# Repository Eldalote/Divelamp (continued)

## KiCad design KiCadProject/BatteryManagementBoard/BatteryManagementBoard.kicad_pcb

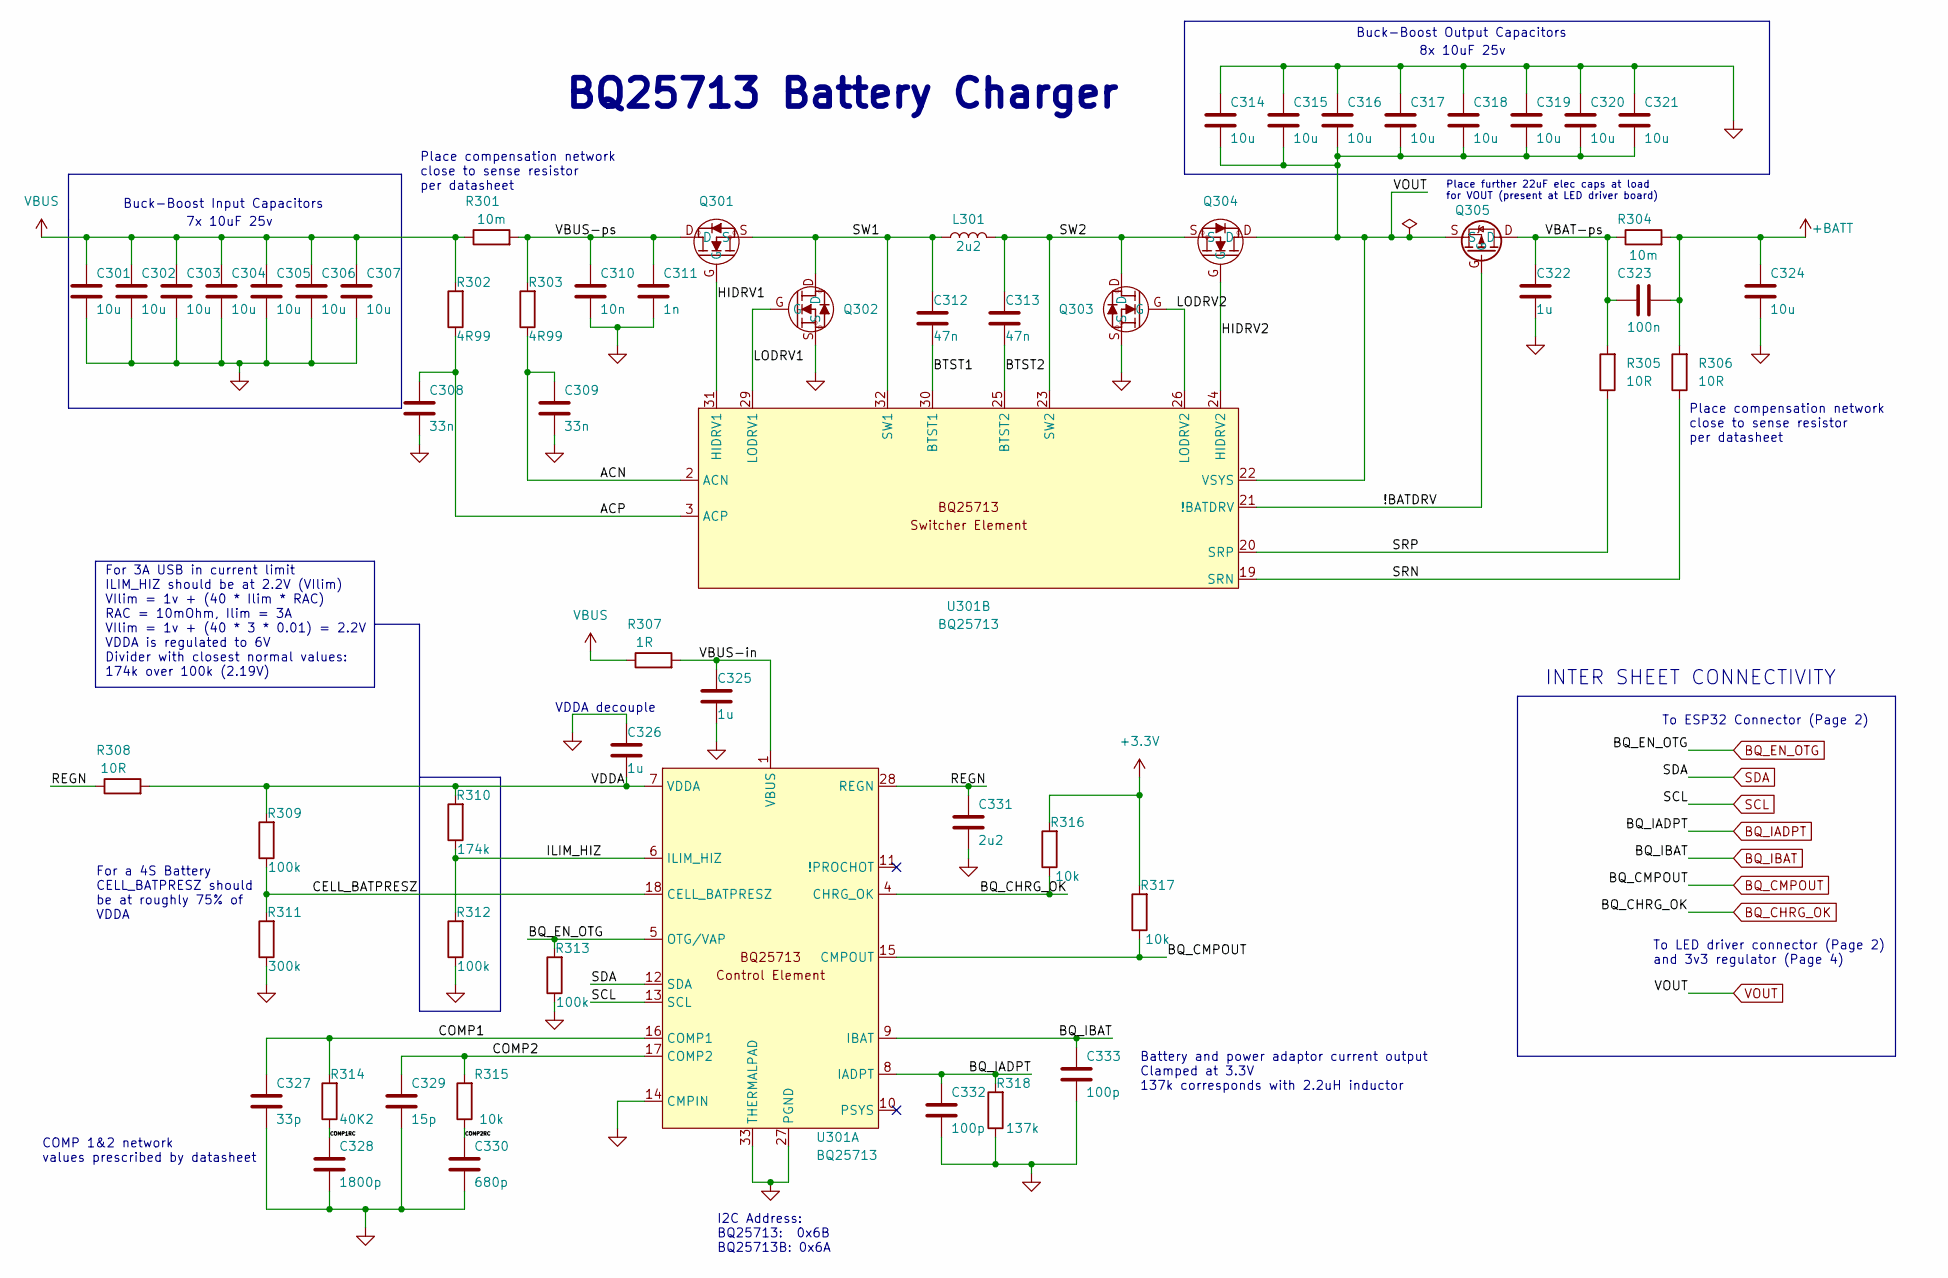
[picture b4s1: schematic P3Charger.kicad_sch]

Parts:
C301, C302, C303, C304, C305, C306, C307, C314, C315, C316, C317, C318, C319, C320, C321, C324: 10u; C_0805_2012Metric
C308, C309: 33n; C_0402_1005Metric
C310: 10n; C_0402_1005Metric
C311: 1n; C_0402_1005Metric
C312, C313: 47n; C_0402_1005Metric
C322, C325, C326: 1u; C_0603_1608Metric
C323: 100n; C_0402_1005Metric
C327: 33p; C_0402_1005Metric
C328: 1800p; C_0402_1005Metric
C329: 15p; C_0402_1005Metric
C330: 680p; C_0402_1005Metric
C331: 2u2; C_0603_1608Metric
C332, C333: 100p; C_0402_1005Metric
L301: 2u2; SRP-1265C
Q301, Q302, Q303, Q304: NFET_Gatenames; DFN3x3A_8L_EP1_P
Q305: PMOS_Gatenames; DFN3x3A_8L_EP1_P
R301, R304: 10m; R_1206_3216Metric
R302, R303: 4R99; R_0402_1005Metric
R305, R306, R308: 10R; R_0402_1005Metric
R307: 1R; R_0603_1608Metric
R309, R312, R313: 100k; R_0402_1005Metric
R310: 174k; R_0402_1005Metric
R311: 300k; R_0402_1005Metric
R314: 40K2; R_0402_1005Metric
R315, R316, R317: 10k; R_0402_1005Metric
R318: 137k; R_0402_1005Metric
U301: BQ25713; Texas_S-PWQFN-N32_EP2.8x2.8mm

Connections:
+3.3V: R316.2, R317.2; also elsewhere on the board
+BATT: C323.2, C324.1, R304.2, R306.2; also elsewhere on the board
/P3-Charger/!BATDRV: Q305.G, U301.21 (!BATDRV)
/P3-Charger/ACN: C309.1, R303.1, U301.2 (ACN)
/P3-Charger/ACP: C308.1, R302.1, U301.3 (ACP)
/P3-Charger/BTST1: C312.2, U301.30 (BTST1)
/P3-Charger/BTST2: C313.2, U301.25 (BTST2)
/P3-Charger/CELL_BATPRESZ: R309.1, R311.2, U301.18 (CELL_BATPRESZ)
/P3-Charger/COMP1: C327.1, R314.2, U301.16 (COMP1)
/P3-Charger/COMP1RC: C328.1, R314.1
/P3-Charger/COMP2: C329.1, R315.2, U301.17 (COMP2)
/P3-Charger/COMP2RC: C330.1, R315.1
/P3-Charger/HIDRV1: Q301.G, U301.31 (HIDRV1)
/P3-Charger/HIDRV2: Q304.G, U301.24 (HIDRV2)
/P3-Charger/ILIM_HIZ: R310.1, R312.2, U301.6 (ILIM_HIZ)
/P3-Charger/LODRV1: Q302.G, U301.29 (LODRV1)
/P3-Charger/LODRV2: Q303.G, U301.26 (LODRV2)
/P3-Charger/REGN: C331.1, R308.1, U301.28 (REGN)
/P3-Charger/SRN: R306.1, U301.19 (SRN)
/P3-Charger/SRP: R305.1, U301.20 (SRP)
/P3-Charger/SW1: C312.1, L301.1, Q301.S, Q302.D, U301.32 (SW1)
/P3-Charger/SW2: C313.1, L301.2, Q303.D, Q304.S, U301.23 (SW2)
/P3-Charger/VBAT-ps: C322.1, C323.1, Q305.D, R304.1, R305.2
/P3-Charger/VBUS-in: C325.1, R307.2, U301.1 (VBUS)
/P3-Charger/VBUS-ps: C310.1, C311.1, Q301.D, R301.2, R303.2
/P3-Charger/VDDA: C326.1, R308.2, R309.2, R310.2, U301.7 (VDDA)
BQ_CHRG_OK: R316.1, U301.4 (CHRG_OK); also elsewhere on the board
BQ_CMPOUT: R317.1, U301.15 (CMPOUT); also elsewhere on the board
BQ_EN_OTG: R313.2, U301.5 (OTG/VAP); also elsewhere on the board
BQ_IADPT: C332.1, R318.2, U301.8 (IADPT); also elsewhere on the board
BQ_IBAT: C333.1, U301.9 (IBAT); also elsewhere on the board
GND: C301.2, C302.2, C303.2, C304.2, C305.2, C306.2, C307.2, C308.2, C309.2, C310.2, C311.2, C314.1, C315.1, C316.1, C317.1, C318.1, C319.1, C320.1, C321.1, C322.2, C324.2, C325.2, C326.2, C327.2, C328.2, C329.2, C330.2, C331.2, C332.2, C333.2, Q302.S, Q303.S, R311.1, R312.1, R313.1, R318.1, U301.14 (CMPIN), U301.27 (PGND), U301.33 (THERMALPAD); also elsewhere on the board
SCL: U301.13 (SCL); also elsewhere on the board
SDA: U301.12 (SDA); also elsewhere on the board
VBUS: C301.1, C302.1, C303.1, C304.1, C305.1, C306.1, C307.1, R301.1, R302.2, R307.1; also elsewhere on the board
VOUT: C314.2, C315.2, C316.2, C317.2, C318.2, C319.2, C320.2, C321.2, Q304.D, Q305.S, U301.22 (VSYS); also elsewhere on the board

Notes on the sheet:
To LED driver connector (Page 2) and 3v3 regulator (Page 4)
Buck-Boost Input Capacitors
INTER SHEET CONNECTIVITY
For a 4S Battery CELL_BATPRESZ should be at roughly 75% of VDDA
7x 10uF 25v
8x 10uF 25v
COMP 1&2 network values prescribed by datasheet
Place further 22uF elec caps at load for VOUT (present at LED driver board)
BQ25713 Battery Charger
VDDA decouple
To ESP32 Connector (Page 2)
Place compensation network close to sense resistor per datasheet
Buck-Boost Output Capacitors
Battery and power adaptor current output Clamped at 3.3V 137k corresponds with 2.2uH inductor
I2C Address: BQ25713: 0x6B BQ25713B: 0x6A
For 3A USB in current limit ILIM_HIZ should be at 2.2V (VIlim) VIlim = 1v + (40 * Ilim * RAC) RAC = 10mOhm, Ilim = 3A VIlim = 1v + (40 * 3 * 0.01) = 2.2V VDDA is regulated to 6V Divider with closest normal values: 174k over 100k (2.19V)

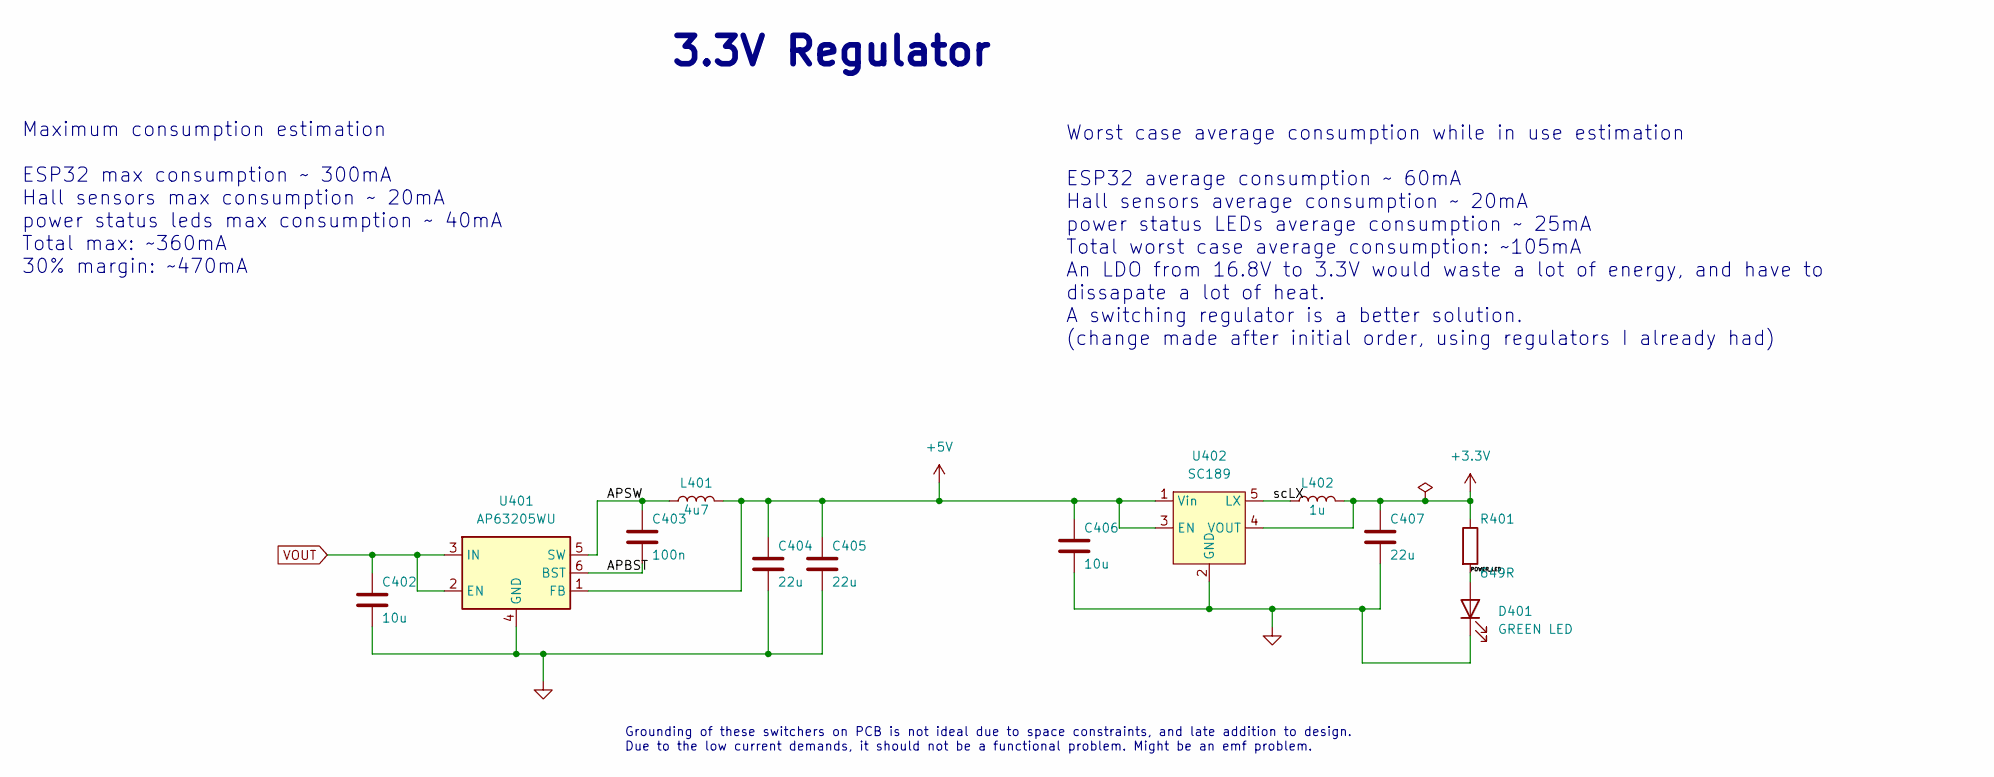
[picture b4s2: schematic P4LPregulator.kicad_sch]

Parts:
C402, C406: 10u; C_0805_2012Metric
C403: 100n; C_0402_1005Metric
C404, C405, C407: 22u; C_0805_2012Metric
D401: GREEN LED; LED_0805_2012Metric
L401: 4u7; L_1210_3225Metric
L402: 1u; L_1210_3225Metric
R401: 649R; R_0402_1005Metric
U401: AP63205WU; TSOT-23-6
U402: SC189; SOT-23-5

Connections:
+3.3V: C407.1, L402.2, R401.1, U402.4 (VOUT); also elsewhere on the board
+5V: C404.1, C405.1, C406.1, L401.2, U401.1 (FB), U402.1 (Vin), U402.3 (EN)
/P4 - 3V3 Regulator/APBST: C403.2, U401.6 (BST)
/P4 - 3V3 Regulator/APSW: C403.1, L401.1, U401.5 (SW)
/P4 - 3V3 Regulator/POWER_LED: D401.2 (A), R401.2
/P4 - 3V3 Regulator/scLX: L402.1, U402.5 (LX)
GND: C402.2, C404.2, C405.2, C406.2, C407.2, D401.1 (K), U401.4 (GND), U402.2 (GND); also elsewhere on the board
VOUT: C402.1, U401.2 (EN), U401.3 (IN); also elsewhere on the board

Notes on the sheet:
Worst case average consumption while in use estimation ESP32 average consumption ~ 60mA Hall sensors average consumption ~ 20mA power status LEDs average consumption ~ 25mA Total worst case average consumption: ~105mA An LDO from 16.8V to 3.3V would waste a lot of energy, and have to dissapate a lo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
Grounding of these switchers on PCB is not ideal due to space constraints, and late addition to design. Due to the low current demands, it should not be a functional problem. Might be an emf problem.
Maximum consumption estimation ESP32 max consumption ~ 300mA Hall sensors max consumption ~ 20mA power status leds max consumption ~ 40mA Total max: ~360mA 30% margin: ~470mA
3.3V Regulator

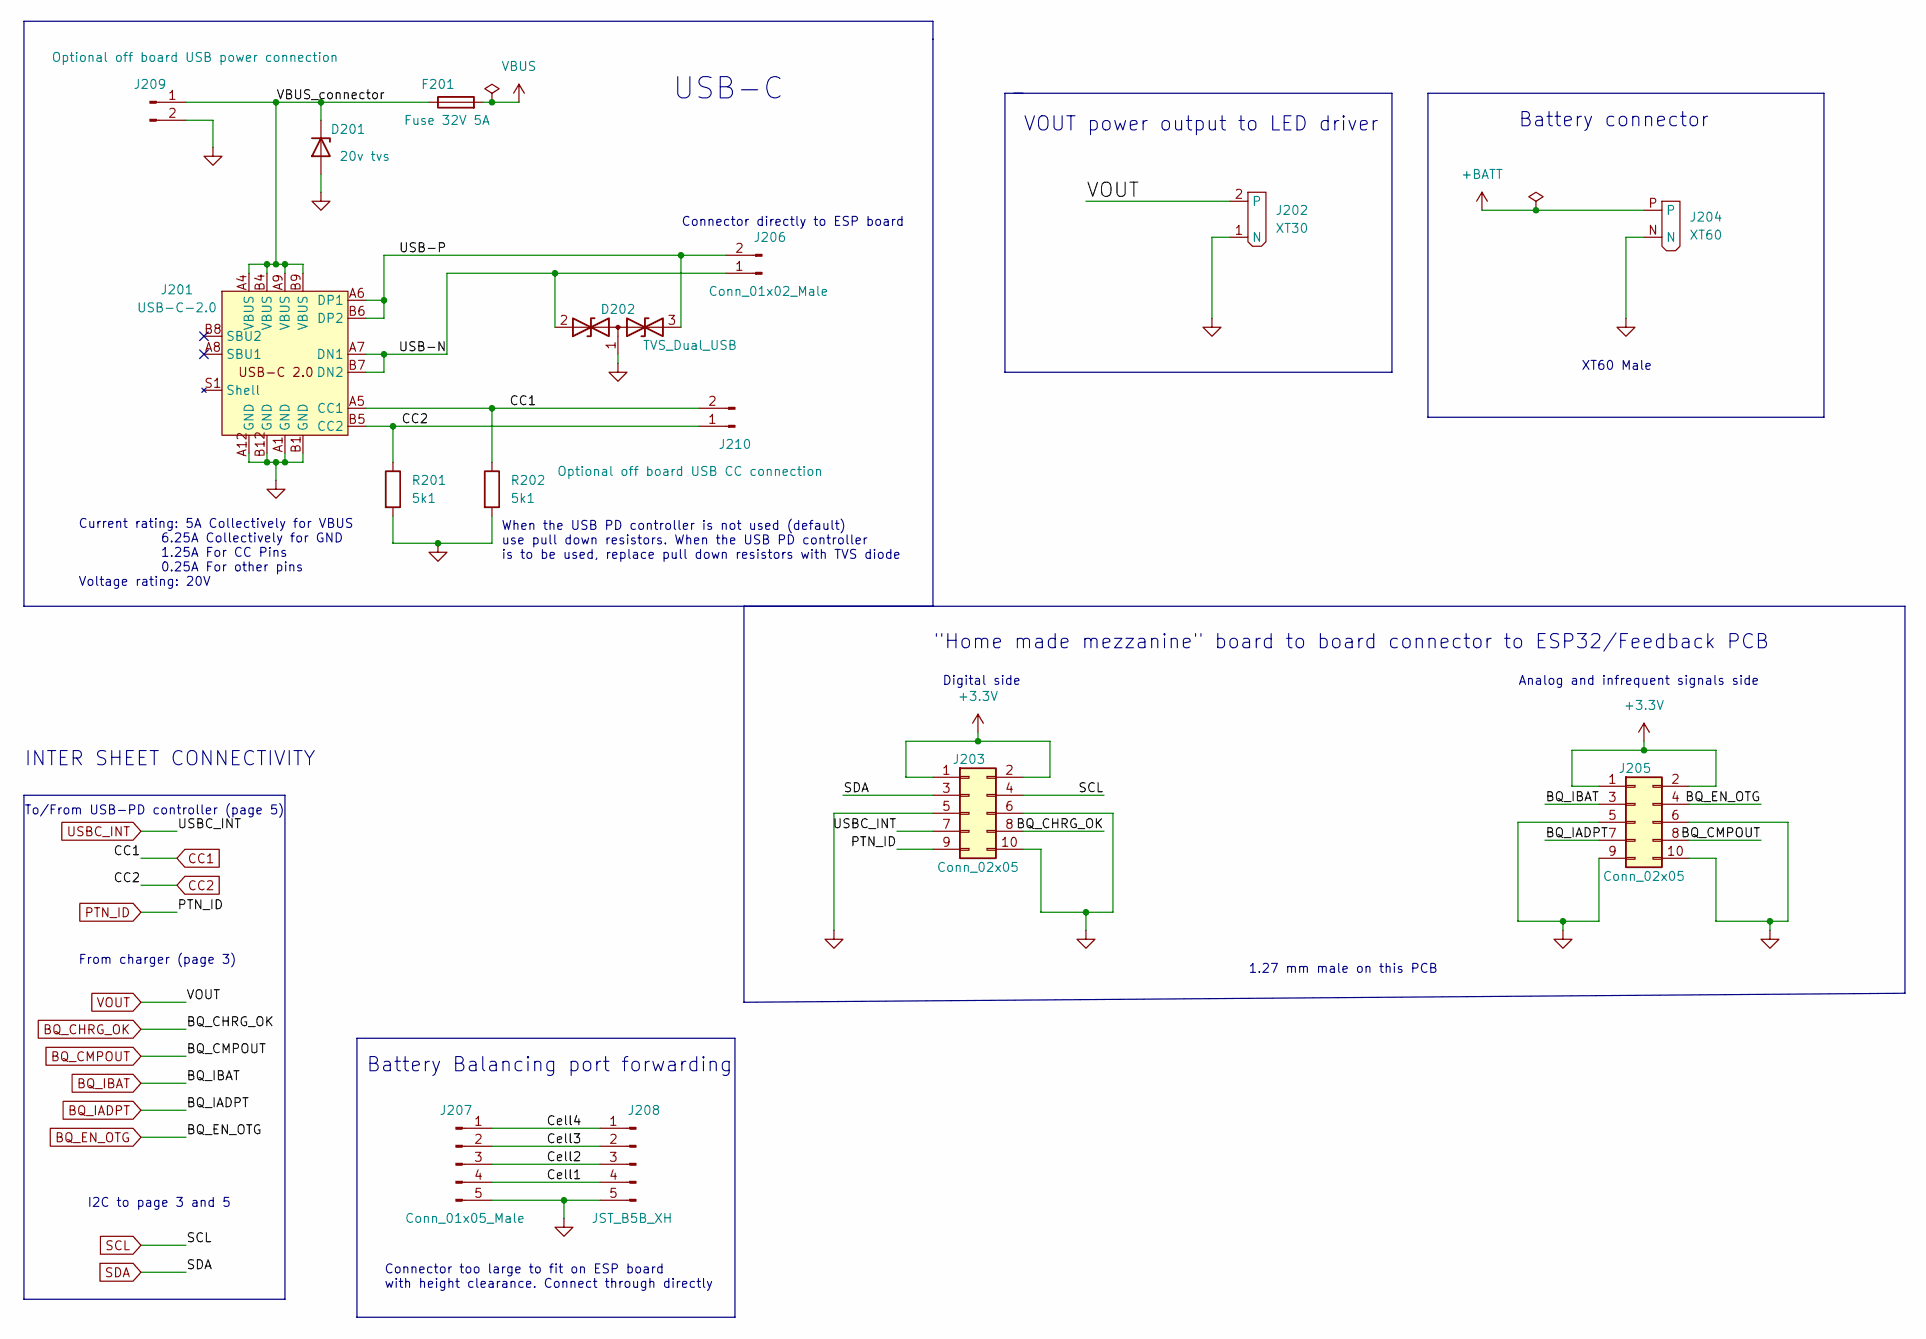
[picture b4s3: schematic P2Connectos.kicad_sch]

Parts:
D201: 20v tvs; D_SMA
D202: TVS_Dual_USB; IC_ESD122DMXR
F201: Fuse 32V 5A; Fuse_0603_1608Metric
J201: USB-C-2.0; GCT_USB4120-03-C_REVA
J202: XT30
J203, J205: Conn_02x05; PinHeader_2x05_P1.27mm_Vertical_SMD
J204: XT60
J206: Conn_01x02_Male; PinHeader_1x02_P1.27mm_Vertical_SMD_Pin1Left
J207: Conn_01x05_Male; PinHeader_1x05_P1.27mm_Vertical_SMD_Pin1Left
J208: JST_B5B_XH; JST_XH_B5B-XH-A_1x05_P2.50mm_Vertical
J209: Optional off board USB power connection; PinHeader_1x02_P2.00mm_Vertical
J210: Optional off board USB CC connection; PinHeader_1x02_P1.00mm_Vertical
R201, R202: 5k1; R_0402_1005Metric

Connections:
+3.3V: J203.1, J203.2, J205.1, J205.2; also elsewhere on the board
+BATT: J204.P; also elsewhere on the board
/P2-Connectors/Cell1: J207.4, J208.4
/P2-Connectors/Cell2: J207.3, J208.3
/P2-Connectors/Cell3: J207.2, J208.2
/P2-Connectors/Cell4: J207.1, J208.1
/P2-Connectors/USB-N: D202.2 (A1), J201.A7 (DN1), J201.B7 (DN2), J206.1
/P2-Connectors/USB-P: D202.3 (A2), J201.A6 (DP1), J201.B6 (DP2), J206.2
/P2-Connectors/VBUS_connector: D201.1 (K), F201.1, J201.A4 (VBUS), J201.A9 (VBUS), J201.B4 (VBUS), J201.B9 (VBUS), J209.1
BQ_CHRG_OK: J203.8; also elsewhere on the board
BQ_CMPOUT: J205.8; also elsewhere on the board
BQ_EN_OTG: J205.4; also elsewhere on the board
BQ_IADPT: J205.7; also elsewhere on the board
BQ_IBAT: J205.3; also elsewhere on the board
CC1: J201.A5 (CC1), J210.2, R202.1; also elsewhere on the board
CC2: J201.B5 (CC2), J210.1, R201.1; also elsewhere on the board
GND: D201.2 (A), D202.1 (common), J201.A1 (GND), J201.A12 (GND), J201.B1 (GND), J201.B12 (GND), J202.1 (N), J203.5, J203.6, J203.10, J204.N, J205.5, J205.6, J205.9, J205.10, J207.5, J208.5, J209.2, R201.2, R202.2; also elsewhere on the board
PTN_ID: J203.9; also elsewhere on the board
SCL: J203.4; also elsewhere on the board
SDA: J203.3; also elsewhere on the board
USBC_INT: J203.7; also elsewhere on the board
VBUS: F201.2; also elsewhere on the board
VOUT: J202.2; also elsewhere on the board

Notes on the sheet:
1.27 mm male on this PCB
VOUT power output to LED driver
Digital side
I2C to page 3 and 5
Connector too large to fit on ESP board with height clearance. Connect through directly
Battery Balancing port forwarding
USB-C
Analog and infrequent signals side
Battery connector
XT60 Male
INTER SHEET CONNECTIVITY
From charger (page 3)
Connector directly to ESP board
Current rating: 5A Collectively for VBUS 6.25A Collectively for GND 1.25A For CC Pins 0.25A For other pins Voltage rating: 20V
To/From USB-PD controller (page 5)
"Home made mezzanine" board to board connector to ESP32/Feedback PCB
When the USB PD controller is not used (default) use pull down resistors. When the USB PD controller is to be used, replace pull down resistors with TVS diode

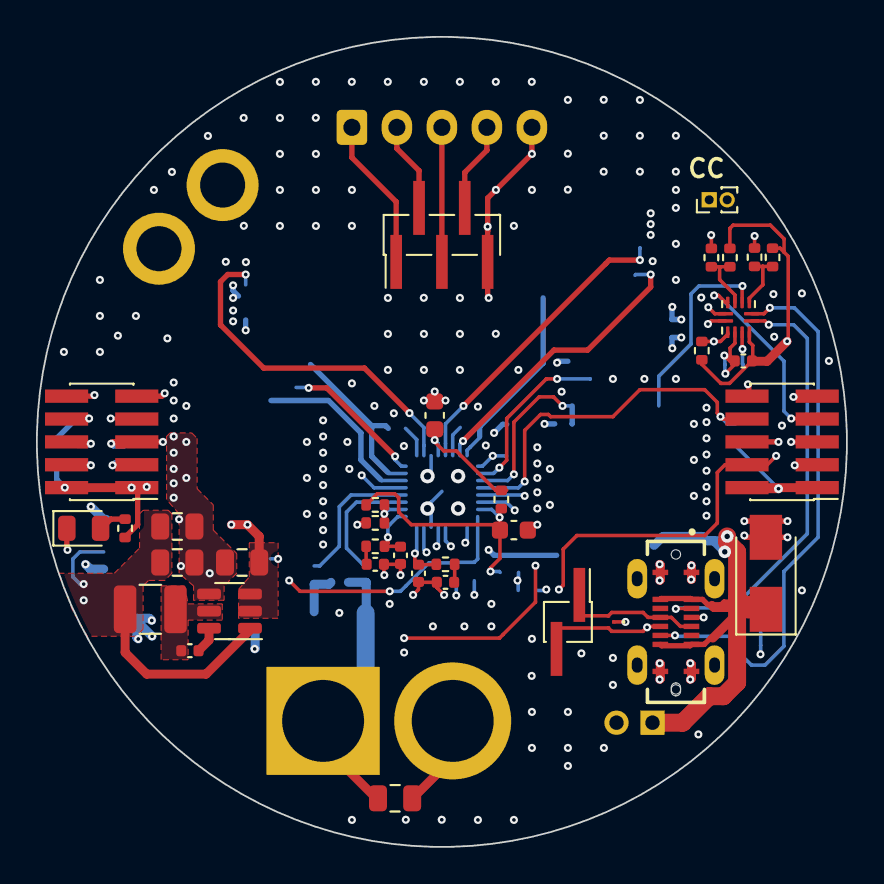
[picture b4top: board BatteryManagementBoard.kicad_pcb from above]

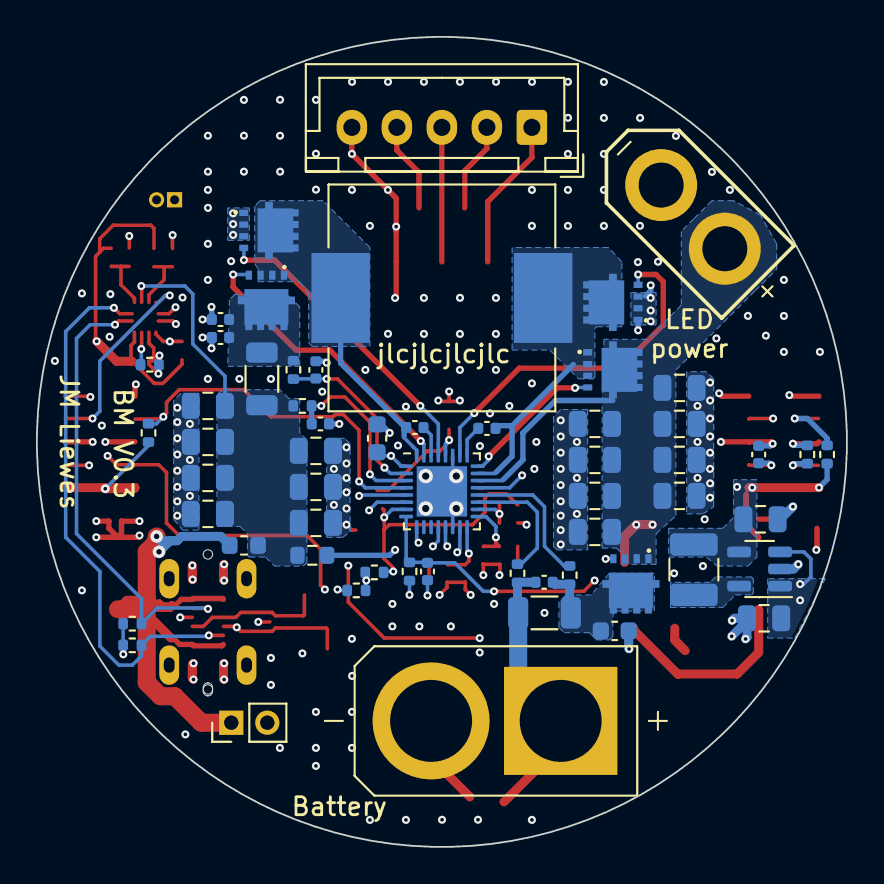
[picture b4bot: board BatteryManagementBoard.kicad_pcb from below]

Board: 6 copper layers, 45.0 x 45.0 mm, 93 parts (58 on the bottom side), 55 nets.

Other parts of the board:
C501: 100n; C_0402_1005Metric
R501, R503, R505, R506: 10k; R_0402_1005Metric
R502, R504: DNP; R_0402_1005Metric
U501: PTN5150; Texas_X2QFN-12_1.6x1.6mm_P0.4mm

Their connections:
+3.3V: C501.1, R501.2, R503.2, R506.2, U501.12 (VDD); also elsewhere on the board
/P5-PTN5150 (Optional)/PTN_ADR: R501.1, R502.2, U501.5 (ADR/CON_DET)
/P5-PTN5150 (Optional)/PTN_ENB: R505.2, U501.11 (ENB)
/P5-PTN5150 (Optional)/PTN_PORT: R503.1, R504.2, U501.3 (PORT)
CC1: U501.1 (CC1); also elsewhere on the board
CC2: U501.2 (CC2); also elsewhere on the board
GND: C501.2, R502.1, R504.1, R505.1, U501.10 (GND); also elsewhere on the board
PTN_ID: R506.1, U501.9 (ID); also elsewhere on the board
SCL: U501.8 (SCL); also elsewhere on the board
SDA: U501.7 (SDA); also elsewhere on the board
USBC_INT: U501.6 (INTB); also elsewhere on the board
VBUS: U501.4 (VBUS_DET); also elsewhere on the board

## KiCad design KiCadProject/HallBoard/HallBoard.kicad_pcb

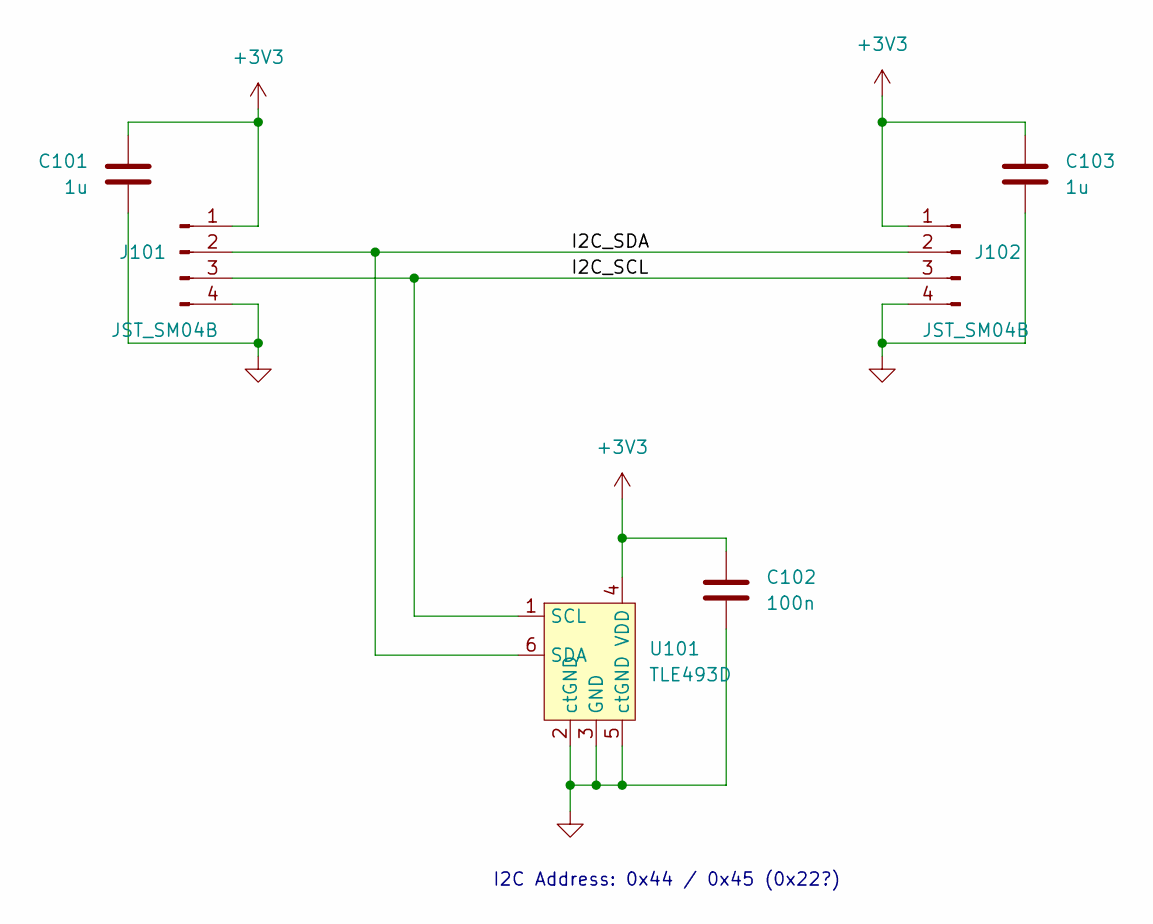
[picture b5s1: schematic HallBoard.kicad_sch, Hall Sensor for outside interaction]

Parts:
C101, C103: 1u; C_0603_1608Metric
C102: 100n; C_0402_1005Metric
J101, J102: JST_SM04B; JST_SH_SM04B-SRSS-TB_1x04-1MP_P1.00mm_Horizontal
U101: TLE493D; SOT-23-6

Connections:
+3V3: C101.1, C102.1, C103.1, J101.1, J102.1, U101.4 (VDD)
/I2C_SCL: J101.3, J102.3, U101.1 (SCL)
/I2C_SDA: J101.2, J102.2, U101.6 (SDA)
GND: C101.2, C102.2, C103.2, J101.4, J102.4, U101.2 (GND), U101.3 (GND), U101.5 (GND)

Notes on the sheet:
I2C Address: 0x44 / 0x45 (0x22?)

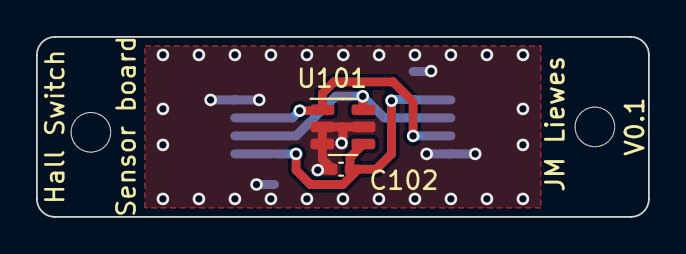
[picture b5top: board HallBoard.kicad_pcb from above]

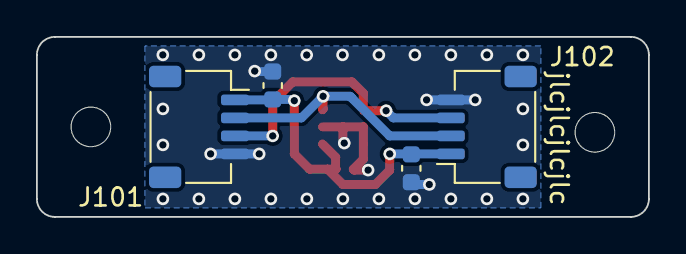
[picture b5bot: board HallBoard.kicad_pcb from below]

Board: 2 copper layers, 34.0 x 10.0 mm, 6 parts (4 on the bottom side), 4 nets.

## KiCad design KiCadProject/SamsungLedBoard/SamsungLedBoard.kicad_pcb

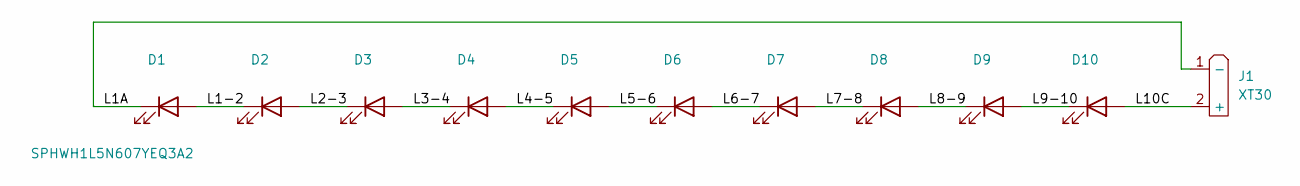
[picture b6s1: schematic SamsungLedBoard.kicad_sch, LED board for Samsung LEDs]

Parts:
D1, D2, D3, D4, D5, D6, D7, D8, D9, D10: SPHWH1L5N607YEQ3A2; LED5050_Samsung_LH502C
J1: XT30

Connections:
/L1-2: D1.2 (A), D2.1 (K)
/L1A: D1.1 (K), J1.1 (-)
/L2-3: D2.2 (A), D3.1 (K)
/L3-4: D3.2 (A), D4.1 (K)
/L4-5: D4.2 (A), D5.1 (K)
/L5-6: D5.2 (A), D6.1 (K)
/L6-7: D6.2 (A), D7.1 (K)
/L7-8: D7.2 (A), D8.1 (K)
/L8-9: D8.2 (A), D9.1 (K)
/L9-10: D9.2 (A), D10.1 (K)
/L10C: D10.2 (A), J1.2 (+)

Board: 2 copper layers, 11 parts (1 on the bottom side), 11 nets, no tracks yet.

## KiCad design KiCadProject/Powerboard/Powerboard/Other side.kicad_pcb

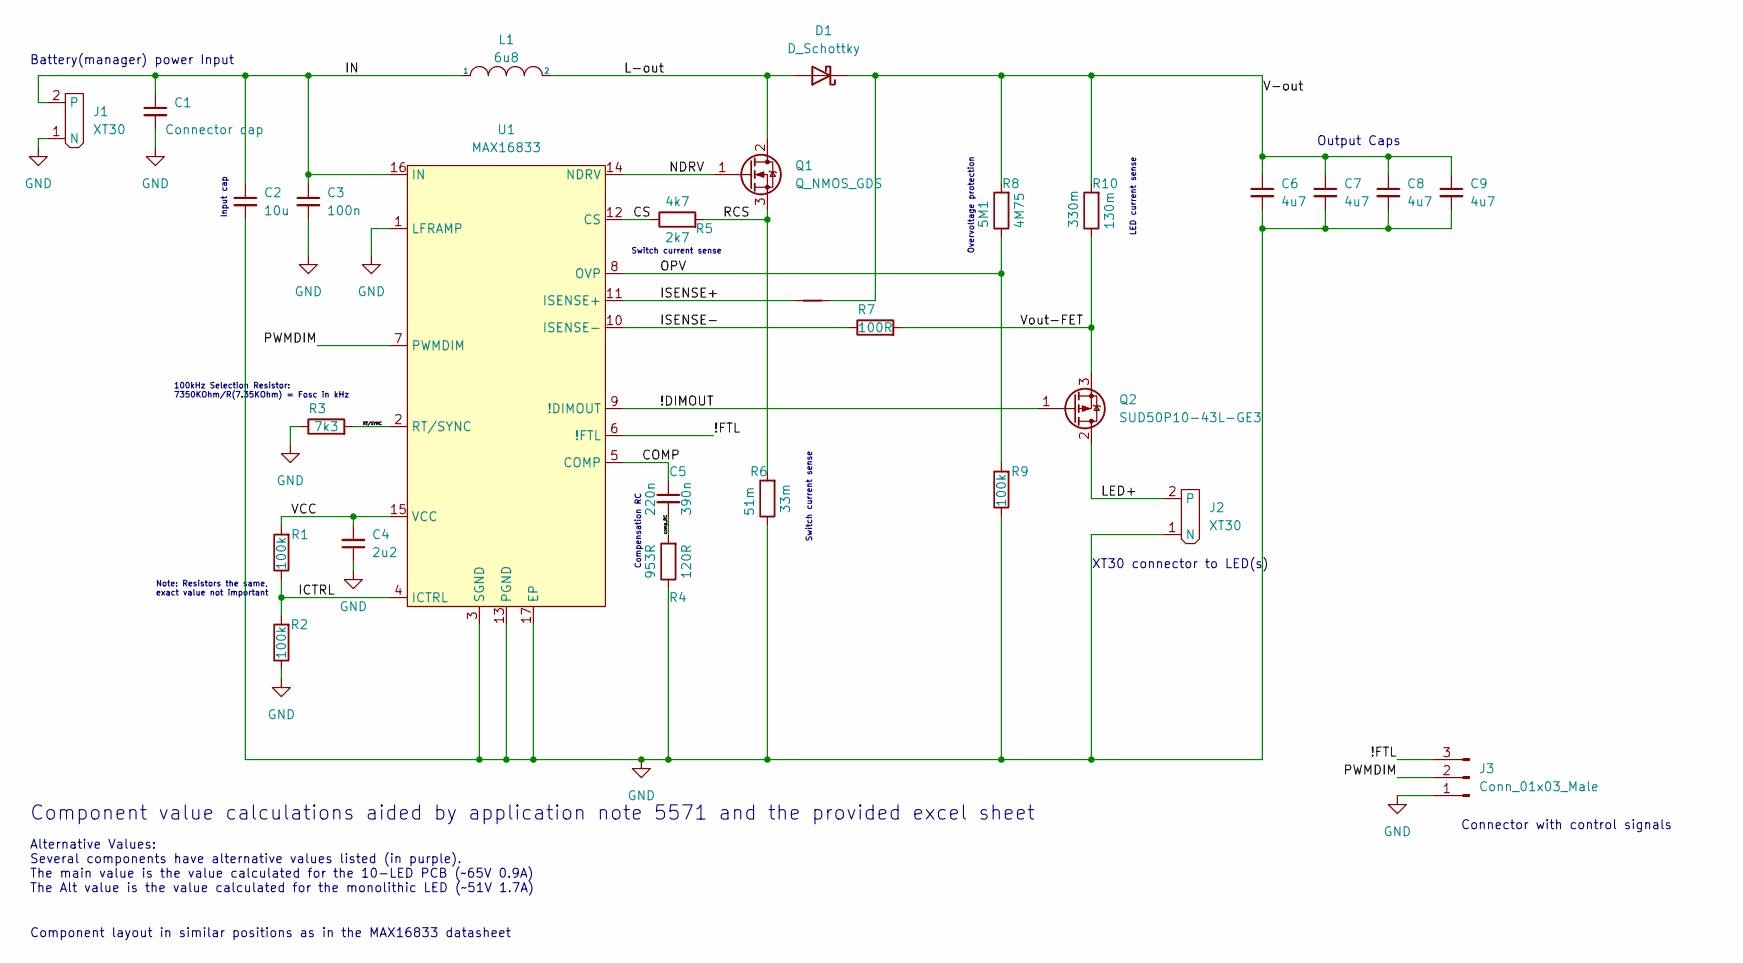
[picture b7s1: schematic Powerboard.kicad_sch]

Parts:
C1: Connector cap; CP_Elec_5x5.3
C2: 10u; C_1206_3216Metric
C3: 100n; C_0402_1005Metric
C4: 2u2; C_0402_1005Metric
C5: 220n; C_0603_1608Metric
C6, C7, C8, C9: 4u7; C_1206_3216Metric
D1: D_Schottky; D_PowerDI-5
J1, J2: XT30
J3: Conn_01x03_Male; PinHeader_1x03_P2.54mm_Vertical
L1: 6u8; SRP-1265C
NT1: NetTie_2; NetTie-2_SMD_Pad0.5mm
Q1: Q_NMOS_GDS; TO-252-2
Q2: SUD50P10-43L-GE3; TO-252-2
R1, R2, R9: 100k; R_0402_1005Metric
R3: 7k3; R_0402_1005Metric
R4: 953R; R_0402_1005Metric
R5: 4k7; R_0402_1005Metric
R6: 51m; R_1206_3216Metric
R7: 100R; R_0603_1608Metric
R8: 5M1; R_0603_1608Metric
R10: 330m; R_1206_3216Metric
U1: MAX16833; HTSSOP-16-1EP_4.4x5mm_P0.65mm_EP3.4x5mm_Mask2.46x2.31mm_The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

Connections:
/!DIMOUT: Q2.1 (G), U1.9 (!DIMOUT)
/!FTL: J3.3, U1.6 (!FTL)
/COMP: C5.1, U1.5 (COMP)
/CS: R5.1, U1.12 (CS)
/ICTRL: R1.1, R2.2, U1.4 (ICTRL)
/IN: C1.1, C2.1, C3.1, J1.2, L1.1, U1.16 (IN)
/ISENSE+: NT1.1, U1.11 (ISENSE+)
/ISENSE-: R7.1, U1.10 (ISENSE-)
/L-out: D1.2 (A), L1.2, Q1.2 (D)
/LED+: J2.2, Q2.2 (D)
/NDRV: Q1.1 (G), U1.14 (NDRV)
/OPV: R8.1, R9.2, U1.8 (OVP)
/PWMDIM: J3.2, U1.7 (PWMDIM)
/RCS: Q1.3 (S), R5.2, R6.2
/RT/SYNC: R3.2, U1.2 (RT/SYNC)
/V-out: C6.1, C7.1, C8.1, C9.1, D1.1 (K), NT1.2, R8.2, R10.2
/VCC: C4.2, R1.2, U1.15 (VCC)
/Vout-FET: Q2.3 (S), R7.2, R10.1
/comp_RC: C5.2, R4.2
GND: C1.2, C2.2, C3.2, C4.1, C6.2, C7.2, C8.2, C9.2, J1.1 (N), J2.1 (N), J3.1, R2.1, R3.1, R4.1, R6.1, R9.1, U1.1 (LFRAMP), U1.3 (SGND), U1.13 (PGND), U1.17 (EP)

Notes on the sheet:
Switch current sense
LED current sense
Compensation RC
XT30 connector to LED(s)
Connector with control signals
Overvoltage protection
Output Caps
Component value calculations aided by application note 5571 and the provided excel sheet
Alternative Values: Several components have alternative values listed (in purple). The main value is the value calculated for the 10-LED PCB (~65V 0.9A) The Alt value is the value calculated for the monolithic LED (~51V 1.7A)
Input cap
Component layout in similar positions as in the MAX16833 datasheet
Note: Resistors the same, exact value not important
100kHz Selection Resistor: 7350KOhm/R(7.35KOhm) = Fosc in kHz
Battery(manager) power Input

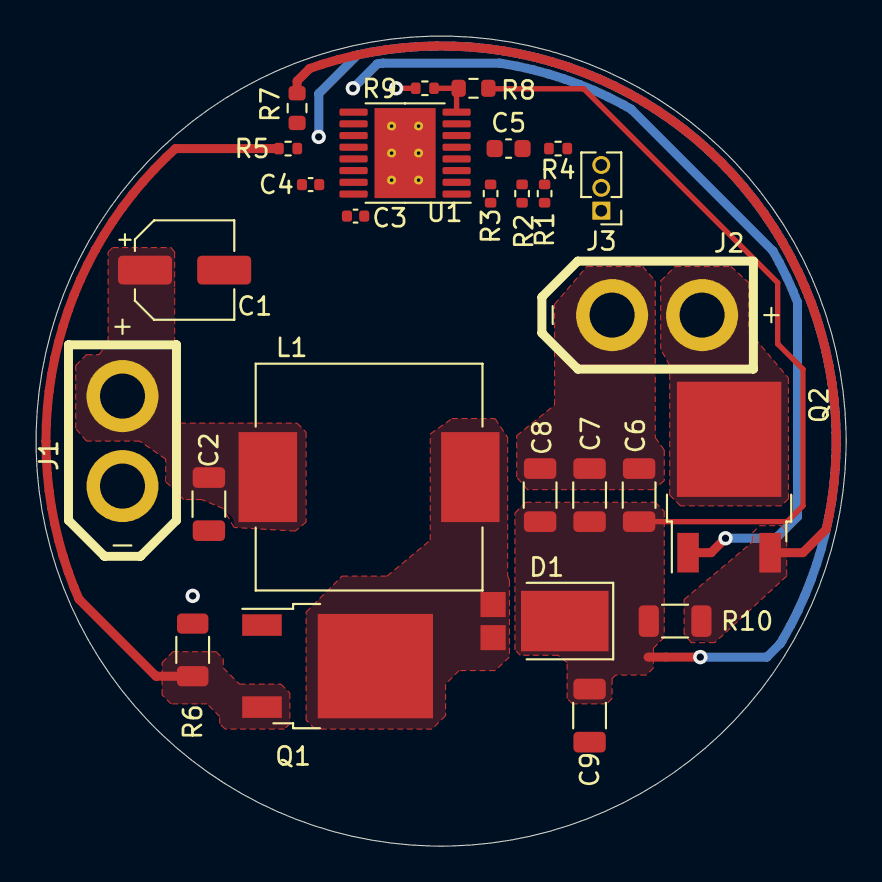
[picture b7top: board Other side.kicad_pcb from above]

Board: 4 copper layers, 45.0 x 45.0 mm, 28 parts (0 on the bottom side), 20 nets.

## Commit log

2022-11-14 Working on the component selection for the max16733
2022-11-16 Passive components selected, only fets and diode to go
2022-11-21 Component selection for max16833 done?
2022-12-01 Refinement work, and start PCB layout
2022-12-02 Much more refinement. Re-selected some components for more logical ones. Got all 3d models in place.
2022-12-03 Should be final placement on powerboard now, just finishing touches left.
2022-12-05 Led driver board v0.1 done
2022-12-09 Started on the battery management board
2022-12-14 BQ25713 layout start
2022-12-16 BQ25713 and LDO done? Stm32 next I think
2022-12-21 Change to design: No more STM32, just use resistors for USB-C PD, en move the battery cell measuring and leveling to the other board.
2023-01-04 jan 4
2023-01-05 ESP board layout mostly done. Small updates to battery management board
2023-01-08 Tweaking
2023-01-09 Final touches before component order and PCB layout
2023-01-09 Final tweaks before component order and PCB completion mk2
2023-01-12 Components selected, MfID added to schematics, and components ordered
2023-01-16 Layout on the battery management board
2023-01-19 Routed Bat management (replaced TUSB because it physically can't be routed with constraints)
2023-01-25 Finished v0.1 of BatMan PCB, started layout of ESP PCB
2023-01-26 Finished V0.1 of ESP PCB
2023-02-01 All PCB's should be done. Do a final check before ordering.
2023-02-02 Made ready to order PCBs. Some problems with ordering due to misunderstanding. Thinking about solutions
2023-02-06 Started work on body 3d work
2023-02-23 bodywork
2023-02-27 Body 3d print design work
2023-03-17 Misc
2023-03-20 Housing top
